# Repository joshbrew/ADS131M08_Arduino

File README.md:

# ADS131M08_Arduino
WIP Arduino implementation for the ADS131M08 by TI

Sample is working but not fully. I get readings now.

Adapted from ADS131M04 library by Daniele Valentino Bella, for Imperial College London Rocketry (LGPL). [link](https://github.com/icl-rocketry/ADS131M04-Lib)

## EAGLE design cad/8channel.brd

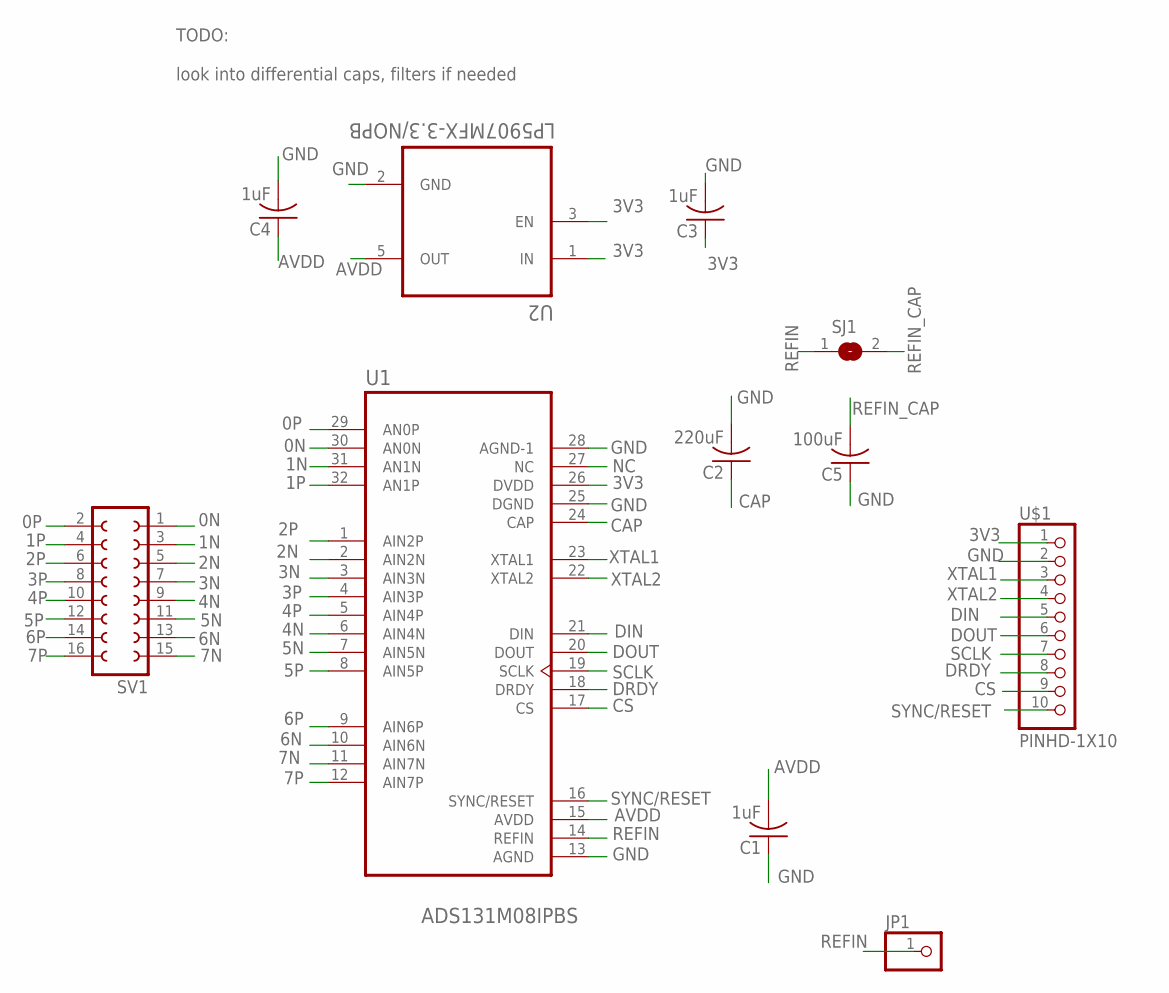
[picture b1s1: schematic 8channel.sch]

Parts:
C1, C3, C4: 1uF; C0603
C2: 220uF; C0603
C5: 100uF; C0603
JP1: PINHD-1X1; 1X01
SJ1: SJ
SV1: FE08-2
U1: ADS131M08IPBS; QFP50P700X700X120-32N
U2: LP5907MFX-3.3/NOPB; SOT95P280X145-5N
U$1: PINHD-1X10; 1X10-BIG

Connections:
0N: SV1.1, U1.30 (AN0N)
0P: SV1.2, U1.29 (AN0P)
1N: SV1.3, U1.31 (AN1N)
1P: SV1.4, U1.32 (AN1P)
2N: SV1.5, U1.2 (AIN2N)
2P: SV1.6, U1.1 (AIN2P)
3N: SV1.7, U1.3 (AIN3N)
3P: SV1.8, U1.4 (AIN3P)
3V3: C3.1, U1.26 (DVDD), U2.1 (IN), U2.3 (EN), U$1.1
4N: SV1.9, U1.6 (AIN4N)
4P: SV1.10, U1.5 (AIN4P)
5N: SV1.11, U1.7 (AIN5N)
5P: SV1.12, U1.8 (AIN5P)
6N: SV1.13, U1.10 (AIN6N)
6P: SV1.14, U1.9 (AIN6P)
7N: SV1.15, U1.11 (AIN7N)
7P: SV1.16, U1.12 (AIN7P)
AVDD: C1.2, C4.1, U1.15 (AVDD), U2.5 (OUT)
CAP: C2.1, U1.24 (CAP)
CS: U1.17 (CS), U$1.9
DIN: U1.21 (DIN), U$1.5
DOUT: U1.20 (DOUT), U$1.6
DRDY: U1.18 (DRDY), U$1.8
GND: C1.1, C2.2, C3.2, C4.2, C5.1, U1.13 (AGND), U1.25 (DGND), U1.28 (AGND-1), U2.2 (GND), U$1.2
NC: U1.27 (NC)
REFIN: JP1.1, SJ1.1, U1.14 (REFIN)
REFIN_CAP: C5.2, SJ1.2
SCLK: U1.19 (SCLK), U$1.7
SYNC/RESET: U1.16 (SYNC/RESET), U$1.10
XTAL1: U1.23 (XTAL1), U$1.3
XTAL2: U1.22 (XTAL2), U$1.4

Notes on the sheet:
TODO: look into differential caps, filters if needed

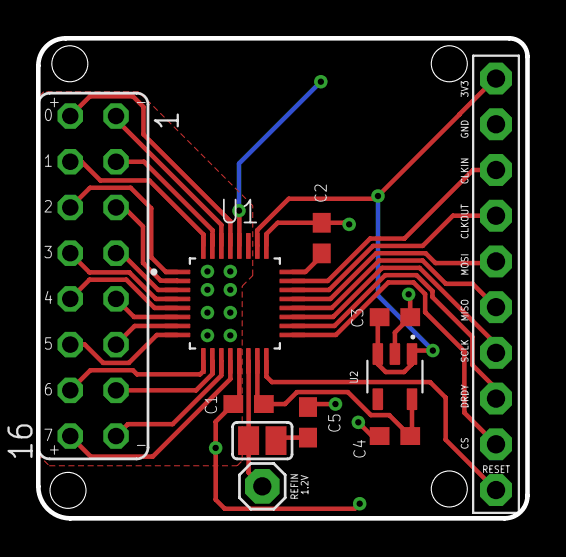
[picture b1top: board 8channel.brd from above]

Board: 2 copper layers, 27.2 x 26.7 mm, 11 parts (0 on the bottom side), 30 nets.

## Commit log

2021-03-08 change to LGPL
2021-04-15 tweak plus ref design
2021-04-19 image
2021-04-19 idiot mistakes
2021-04-19 getting closer (still an idiot)
2021-04-19 we have response!!!!
2021-04-19 nope no we don't
2021-04-29 edit
2021-05-06 minor fixes (still not working)
2021-05-07 working reading
2021-05-23 reading all 8 channels simultaneously
2021-05-23 settings are not working for some reason
2021-05-23 fix settings (resetting at end was dumb)
2021-05-24 faster baud
2021-06-24 add lbr

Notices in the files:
cad/8channel.brd:
MIT LICENSE
